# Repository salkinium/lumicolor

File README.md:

Luminet2 Demonstrator
=====================

The [Luminet2 Smart Pixel][luminet2], developed by [The Media Computing Group][i10], can be used as a stand alone color LED or integrated into more complex communication networks.

This project gives you a starting point of how to use the Smart Pixel with the microcontroller library [xpcc.io][], with support for the color LED, light sensor and serial communication protocols.

Also see my other project with the Pixels, [The Textile Display][].

Organisation
------------

This repository is organized as follows:

-	The *software* folder contains the embedded software for the pixel.

The Luminet2 Smart Pixel was designed by [Mariana Bocoi][bocoi].  
The embedded software and communication protocol was designed by [Niklas Hauser][hauser].

[luminet2]: http://hci.rwth-aachen.de/luminet2
[i10]: http://hci.rwth-aachen.de
[bocoi]: http://hci.rwth-aachen.de/bocoi
[hauser]: http://hci.rwth-aachen.de/hauser
[xpcc.io]: http://xpcc.io
[The Textile Display]: https://github.com/salkinium/textile_display

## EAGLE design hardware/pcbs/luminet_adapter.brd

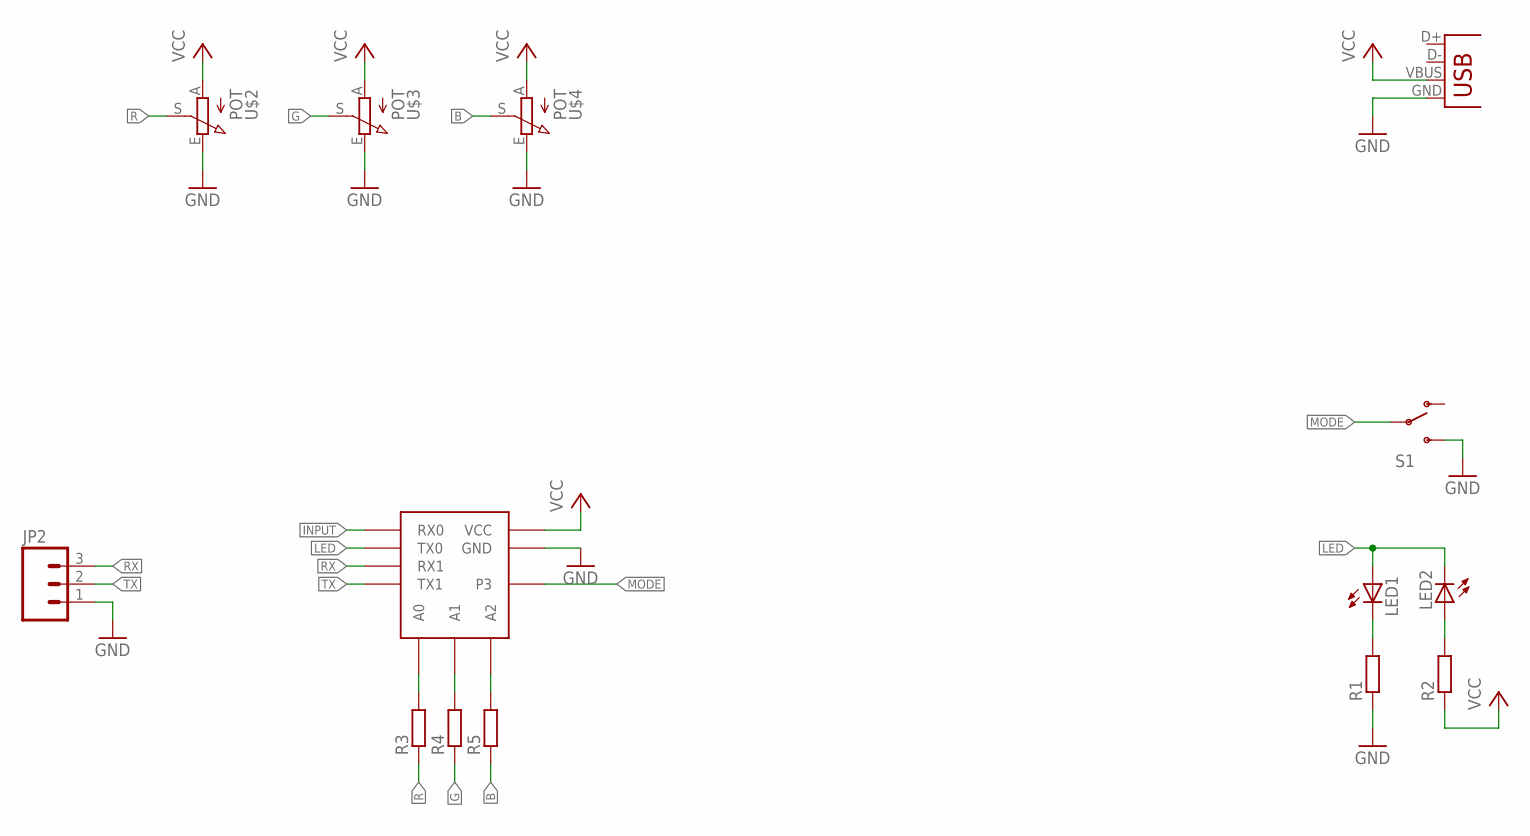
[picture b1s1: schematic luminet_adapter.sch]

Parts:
JP1: USBOLD; USB-MINIB-OLD
JP2: M03LOCK_LONGPADS; 1X03_LOCK_LONGPADS
LED1, LED2: LEDCHIPLED_1206; CHIPLED_1206
R1, R2, R3, R4, R5: R-EU_R0805; R0805
S1: SWITCH-SPDT-SMD-A; SWITCH-SPST-SMD-A
U$1: LUMINET2; LUMINET_ADAPTER
U$2, U$3, U$4: POT; POTENTIOMETER

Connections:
B: R5.1, U$4.S
B1: R5.2, U$1.A2
G: R4.1, U$3.S
G1: R4.2, U$1.A1
GND: JP1.GND, JP2.1, R1.1, S1.3 (S), U$1.GND@1 (GND), U$1.GND@2 (GND), U$1.GND@3 (GND), U$2.E, U$3.E, U$4.E
INPUT: U$1.RX0
LED: LED1.A, LED2.C, U$1.TX0
MODE: S1.2, U$1.P3
unnamed: LED1.C, R1.2
unnamed: LED2.A, R2.2
R: R3.1, U$2.S
R1: R3.2, U$1.A0
RX: JP2.3, U$1.RX1
TX: JP2.2, U$1.TX1
VCC: JP1.VBUS, R2.1, U$1.VCC@1 (VCC), U$1.VCC@2 (VCC), U$1.VCC@3 (VCC), U$2.A, U$3.A, U$4.A

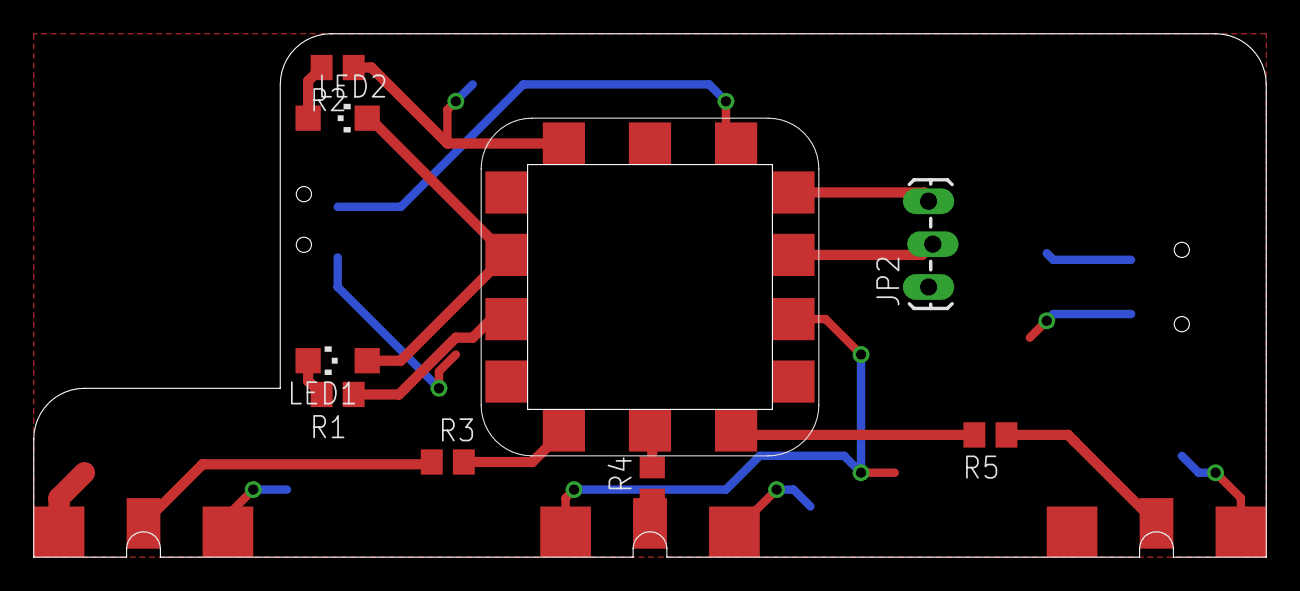
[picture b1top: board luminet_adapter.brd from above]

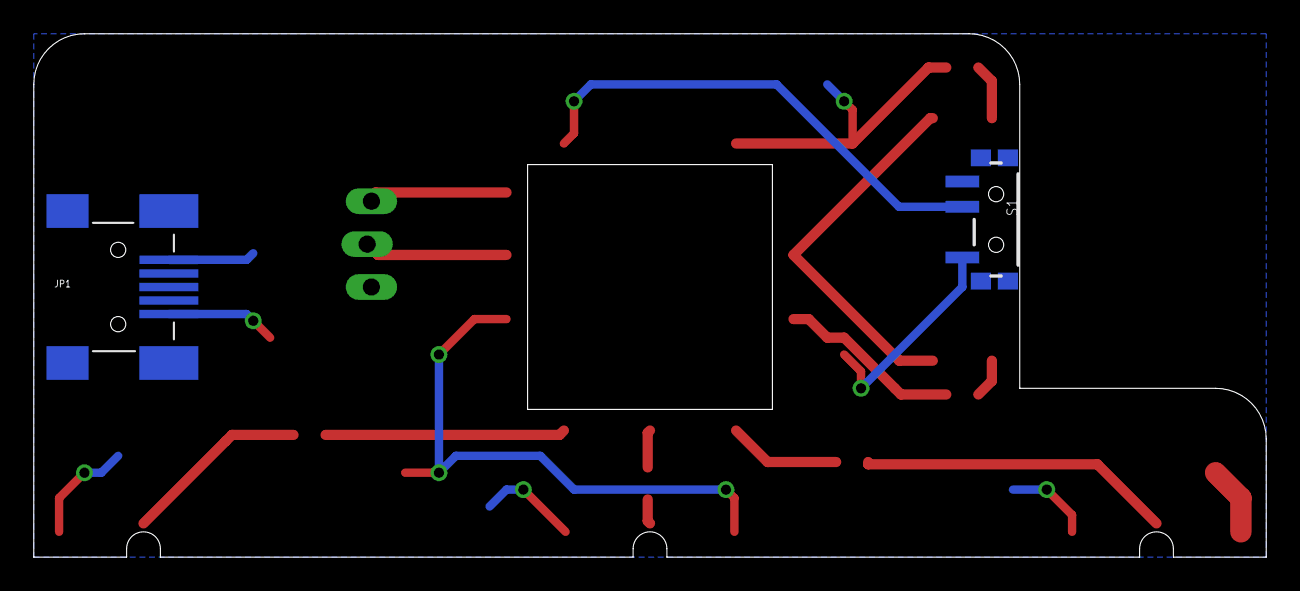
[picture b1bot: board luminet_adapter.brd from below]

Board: 2 copper layers, 73.0 x 31.0 mm, 14 parts (2 on the bottom side), 14 nets.

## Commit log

2013-10-04 Add README.md
2013-10-04 Add xpcc.io submodule.
2013-10-04 Add gitignore, Licence and Software Readme.
2013-10-04 Add source with demo program.
2013-10-04 Set Uart Baudrate to 38.4kBaud, for minimal error.
2013-12-13 Move source folder to dreamer.
2013-12-13 Add Luminet2 Adapter board.
2013-12-13 Add color generator code.
2013-12-13 Update xpcc.io.
2013-12-17 Update for xpcc.io.

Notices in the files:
parts and their libraries:
SparkFun-Connectors: Licensing: CC v3.0 Share-Alike You are welcome to use this library for commercial purposes.
